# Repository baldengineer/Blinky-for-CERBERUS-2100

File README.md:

## Blinky for CERBERUS 2100
Simple board to plug into a [CERBERUS 2100](https://www.thebyteattic.com/p/cerberus-2100.html) and display blinky patterns. It uses a transparent latch (74HVC573) to display the 8-bit data bus on individual LEDs. You can select between the `XCLK` or `XSLC` to drive the display.

The idea is that `XCLK` would continously update with whatever values are on the data bus. Using `XSLC` should only update after a write occurs (but the timing might be off?).

## Future ideas
I may implement a version with a PLD to experiement with programmable logic. 

## Status
Sent rev 1 to the fab. I realize after that I did not provide an easy way to enable the `XE` signal, which turns on the buffers on the CERBERUS 2100. However, there are pads to bodge it.

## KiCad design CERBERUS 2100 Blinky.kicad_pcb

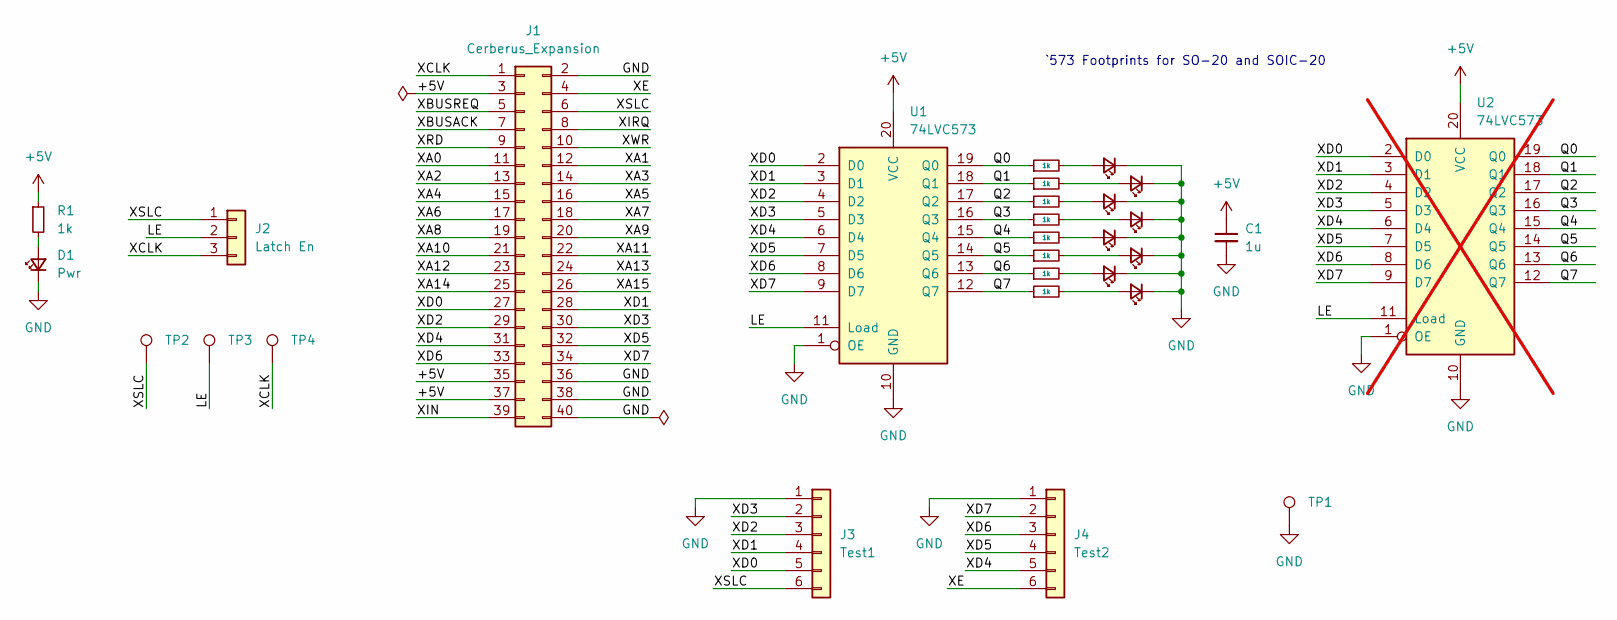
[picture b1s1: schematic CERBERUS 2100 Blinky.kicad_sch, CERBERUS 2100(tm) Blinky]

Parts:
C1: 1u; C_0805_2012Metric_Pad1.18x1.45mm_HandSolder
D1, D2, D3, D4, D5, D6, D7, D8, D9: Pwr; LED_1206_3216Metric_Pad1.42x1.75mm_HandSolder
J1: Cerberus_Expansion; PinSocket_2x20_P2.54mm_Vertical
J2: Latch En; PinHeader_1x03_P2.54mm_Vertical
J3: Test1; PinHeader_1x06_P2.54mm_Vertical
J4: Test2; PinHeader_1x06_P2.54mm_Vertical
R1, R2, R3, R4, R5, R6, R7, R8, R9: 1k; R_0805_2012Metric_Pad1.20x1.40mm_HandSolder
TP1, TP2, TP3, TP4: TestPoint_Harwin; Harwin-S1751-46-Test-Point
U1: 74LVC573; SO-20_5.3x12.6mm_P1.27mm
U2: 74LVC573; SOIC-20W_7.5x12.8mm_P1.27mm; not fitted

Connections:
+5V: C1.1, J1.3, J1.35, J1.37, R1.1, U1.20 (VCC), U2.20 (VCC)
/LE: J2.2, TP3.1, U1.11 (Load), U2.11 (Load)
/Q0: R2.1, U1.19 (Q0), U2.19 (Q0)
/Q1: R3.1, U1.18 (Q1), U2.18 (Q1)
/Q2: R4.1, U1.17 (Q2), U2.17 (Q2)
/Q3: R5.1, U1.16 (Q3), U2.16 (Q3)
/Q4: R6.1, U1.15 (Q4), U2.15 (Q4)
/Q5: R7.1, U1.14 (Q5), U2.14 (Q5)
/Q6: R8.1, U1.13 (Q6), U2.13 (Q6)
/Q7: R9.1, U1.12 (Q7), U2.12 (Q7)
/XA0: J1.11
/XA1: J1.12
/XA2: J1.13
/XA3: J1.14
/XA4: J1.15
/XA5: J1.16
/XA6: J1.17
/XA7: J1.18
/XA8: J1.19
/XA9: J1.20
/XA10: J1.21
/XA11: J1.22
/XA12: J1.23
/XA13: J1.24
/XA14: J1.25
/XA15: J1.26
/XBUSACK: J1.7
/XBUSREQ: J1.5
/XCLK: J1.1, J2.3, TP4.1
/XD0: J1.27, J3.5, U1.2 (D0), U2.2 (D0)
/XD1: J1.28, J3.4, U1.3 (D1), U2.3 (D1)
/XD2: J1.29, J3.3, U1.4 (D2), U2.4 (D2)
/XD3: J1.30, J3.2, U1.5 (D3), U2.5 (D3)
/XD4: J1.31, J4.5, U1.6 (D4), U2.6 (D4)
/XD5: J1.32, J4.4, U1.7 (D5), U2.7 (D5)
/XD6: J1.33, J4.3, U1.8 (D6), U2.8 (D6)
/XD7: J1.34, J4.2, U1.9 (D7), U2.9 (D7)
/XE: J1.4, J4.6
/XIN: J1.39
/XIRQ: J1.8
/XRD: J1.9
/XSLC: J1.6, J2.1, J3.6, TP2.1
/XWR: J1.10
GND: C1.2, D1.1 (K), D2.1 (K), D3.1 (K), D4.1 (K), D5.1 (K), D6.1 (K), D7.1 (K), D8.1 (K), D9.1 (K), J1.2, J1.36, J1.38, J1.40, J3.1, J4.1, TP1.1, U1.1 (OE), U1.10 (GND), U2.1 (OE), U2.10 (GND)
unnamed: D1.2 (A), R1.2
unnamed: D2.2 (A), R2.2
unnamed: D3.2 (A), R3.2
unnamed: D4.2 (A), R4.2
unnamed: D5.2 (A), R5.2
unnamed: D6.2 (A), R6.2
unnamed: D7.2 (A), R7.2
unnamed: D8.2 (A), R8.2
unnamed: D9.2 (A), R9.2

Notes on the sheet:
`573 Footprints for SO-20 and SOIC-20

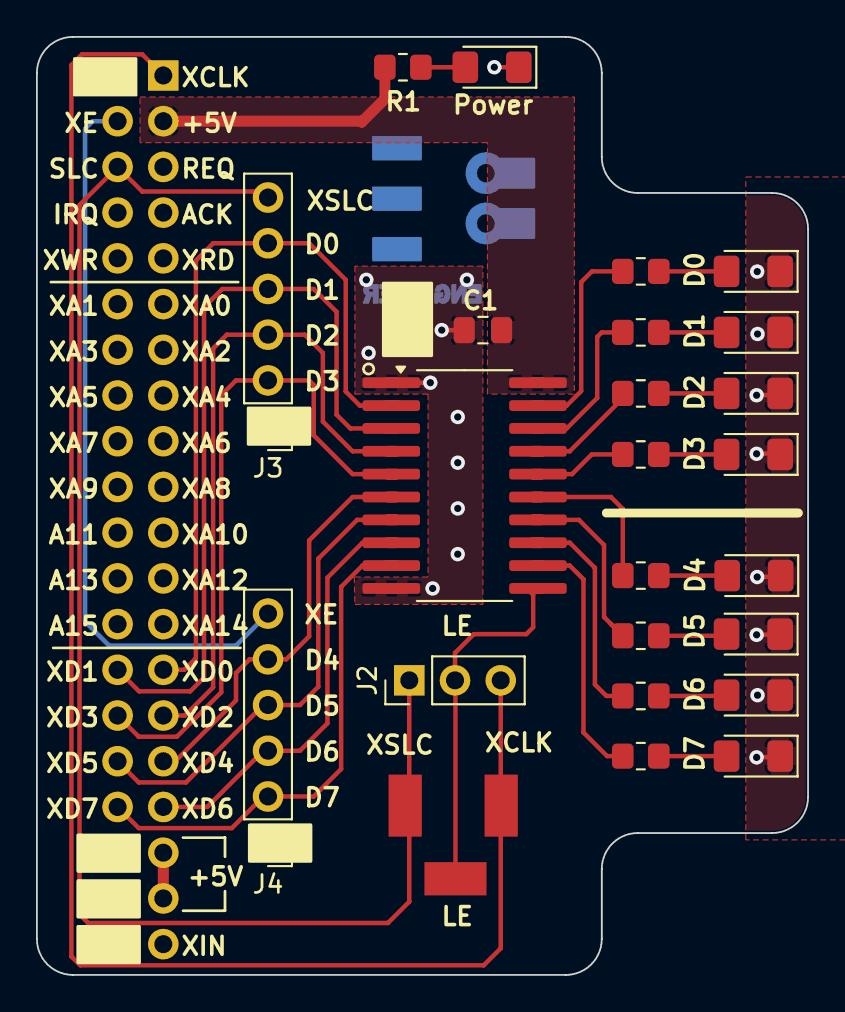
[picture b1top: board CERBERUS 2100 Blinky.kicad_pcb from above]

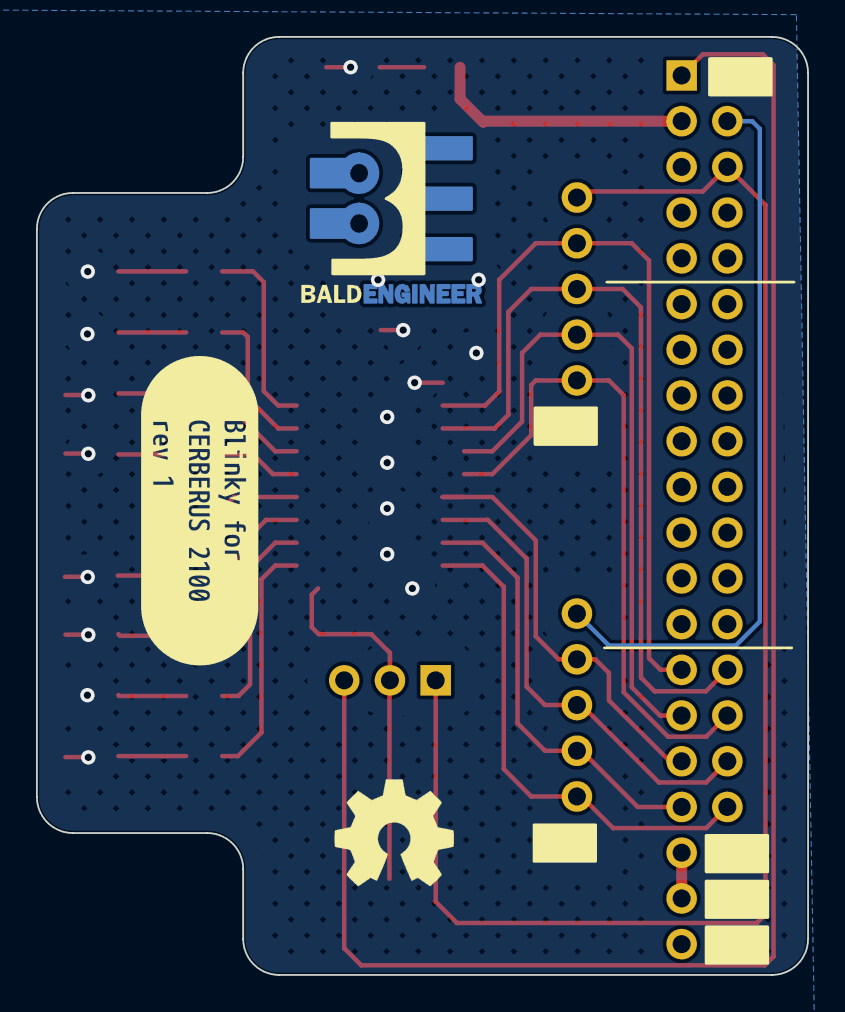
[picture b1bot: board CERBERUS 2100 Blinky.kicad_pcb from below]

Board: 2 copper layers, 42.8 x 52.1 mm, 31 parts (2 on the bottom side), 31 nets.

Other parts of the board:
kibuzzard-663A818A: G***; kibuzzard-663A818A
svg2mod: G***; BE10v2

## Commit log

2024-05-08 rev 1 sent to fab
2024-05-08 added rev1 render
